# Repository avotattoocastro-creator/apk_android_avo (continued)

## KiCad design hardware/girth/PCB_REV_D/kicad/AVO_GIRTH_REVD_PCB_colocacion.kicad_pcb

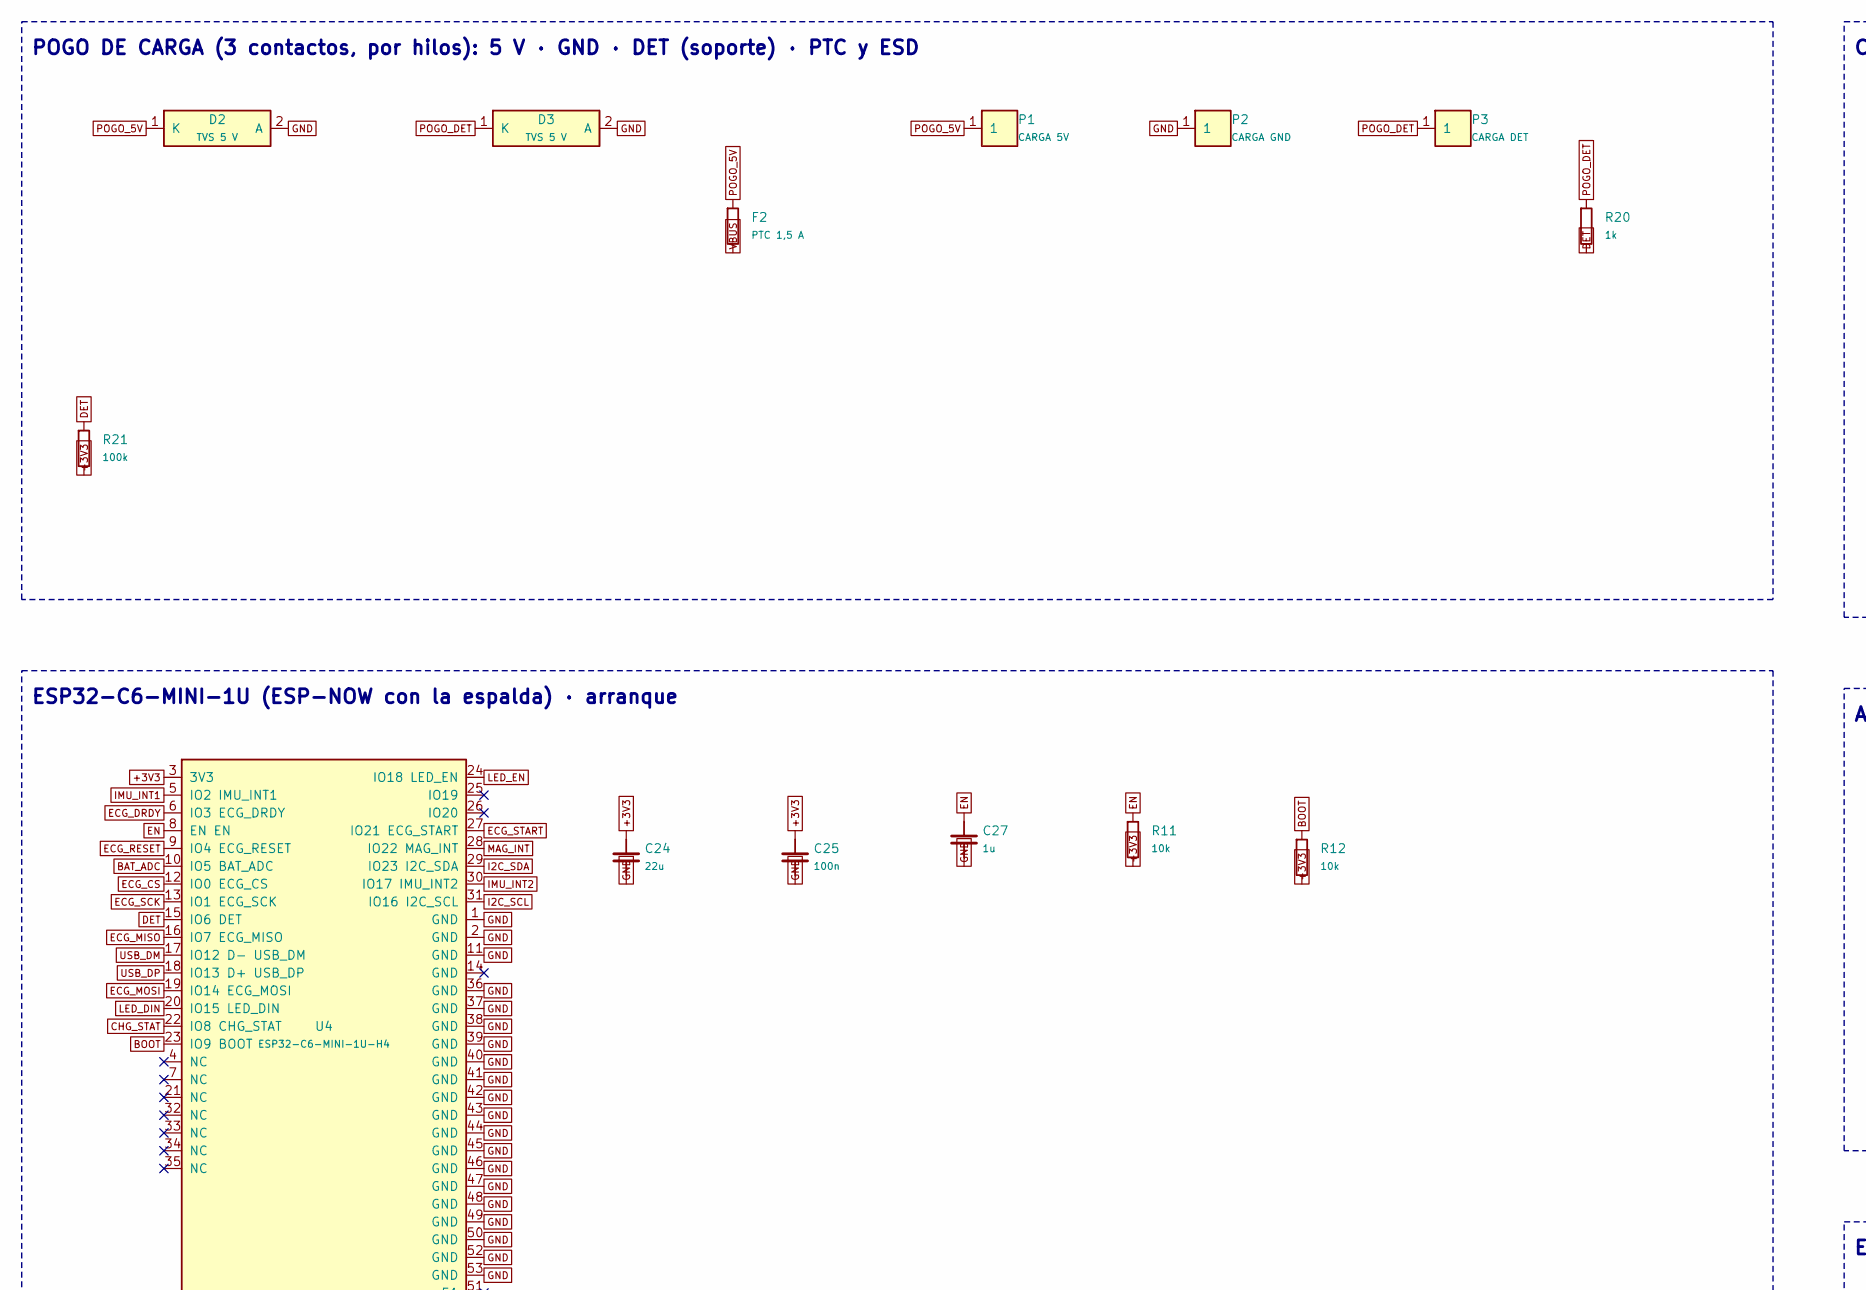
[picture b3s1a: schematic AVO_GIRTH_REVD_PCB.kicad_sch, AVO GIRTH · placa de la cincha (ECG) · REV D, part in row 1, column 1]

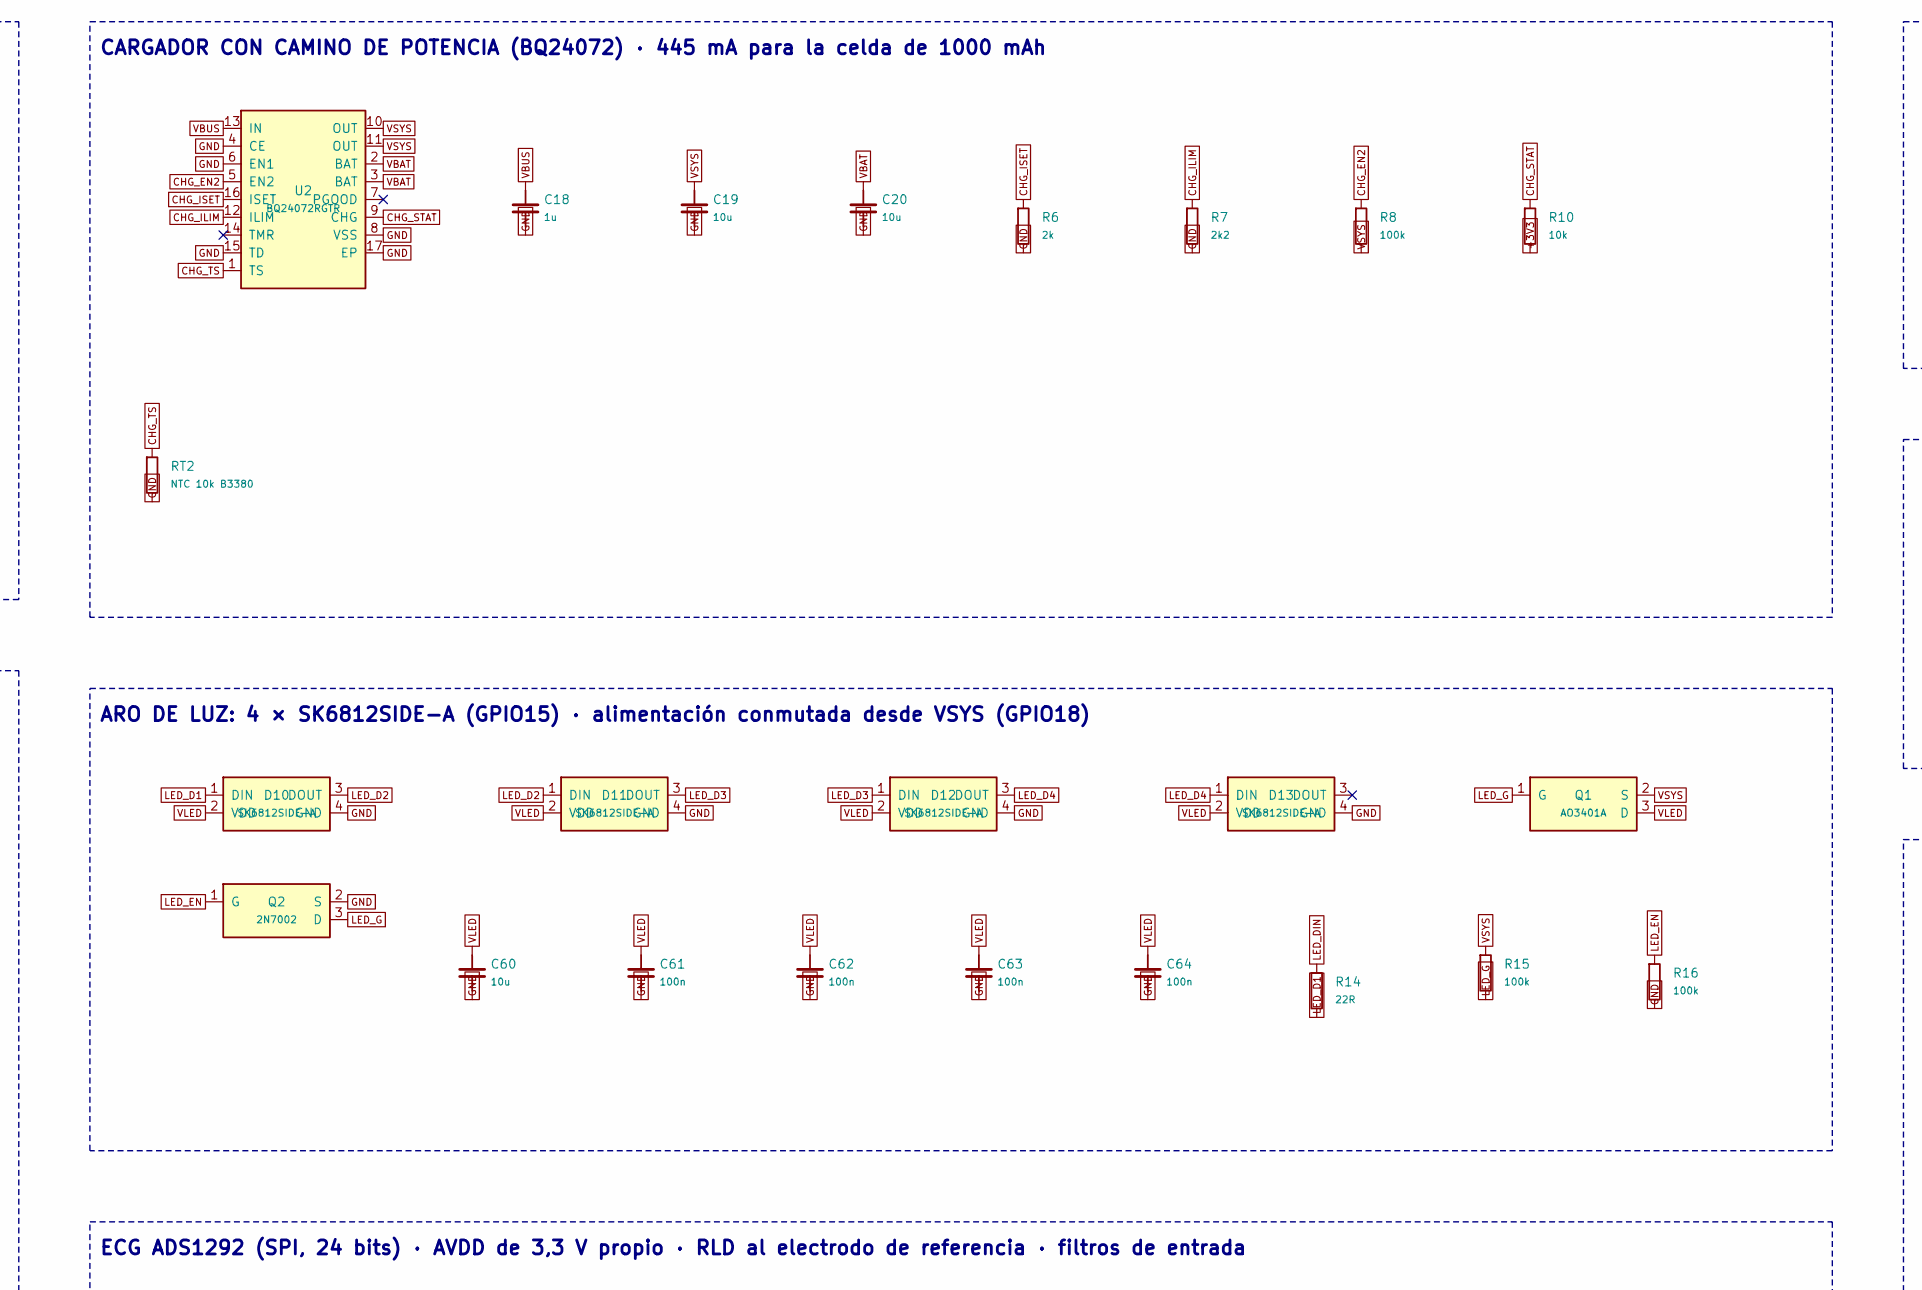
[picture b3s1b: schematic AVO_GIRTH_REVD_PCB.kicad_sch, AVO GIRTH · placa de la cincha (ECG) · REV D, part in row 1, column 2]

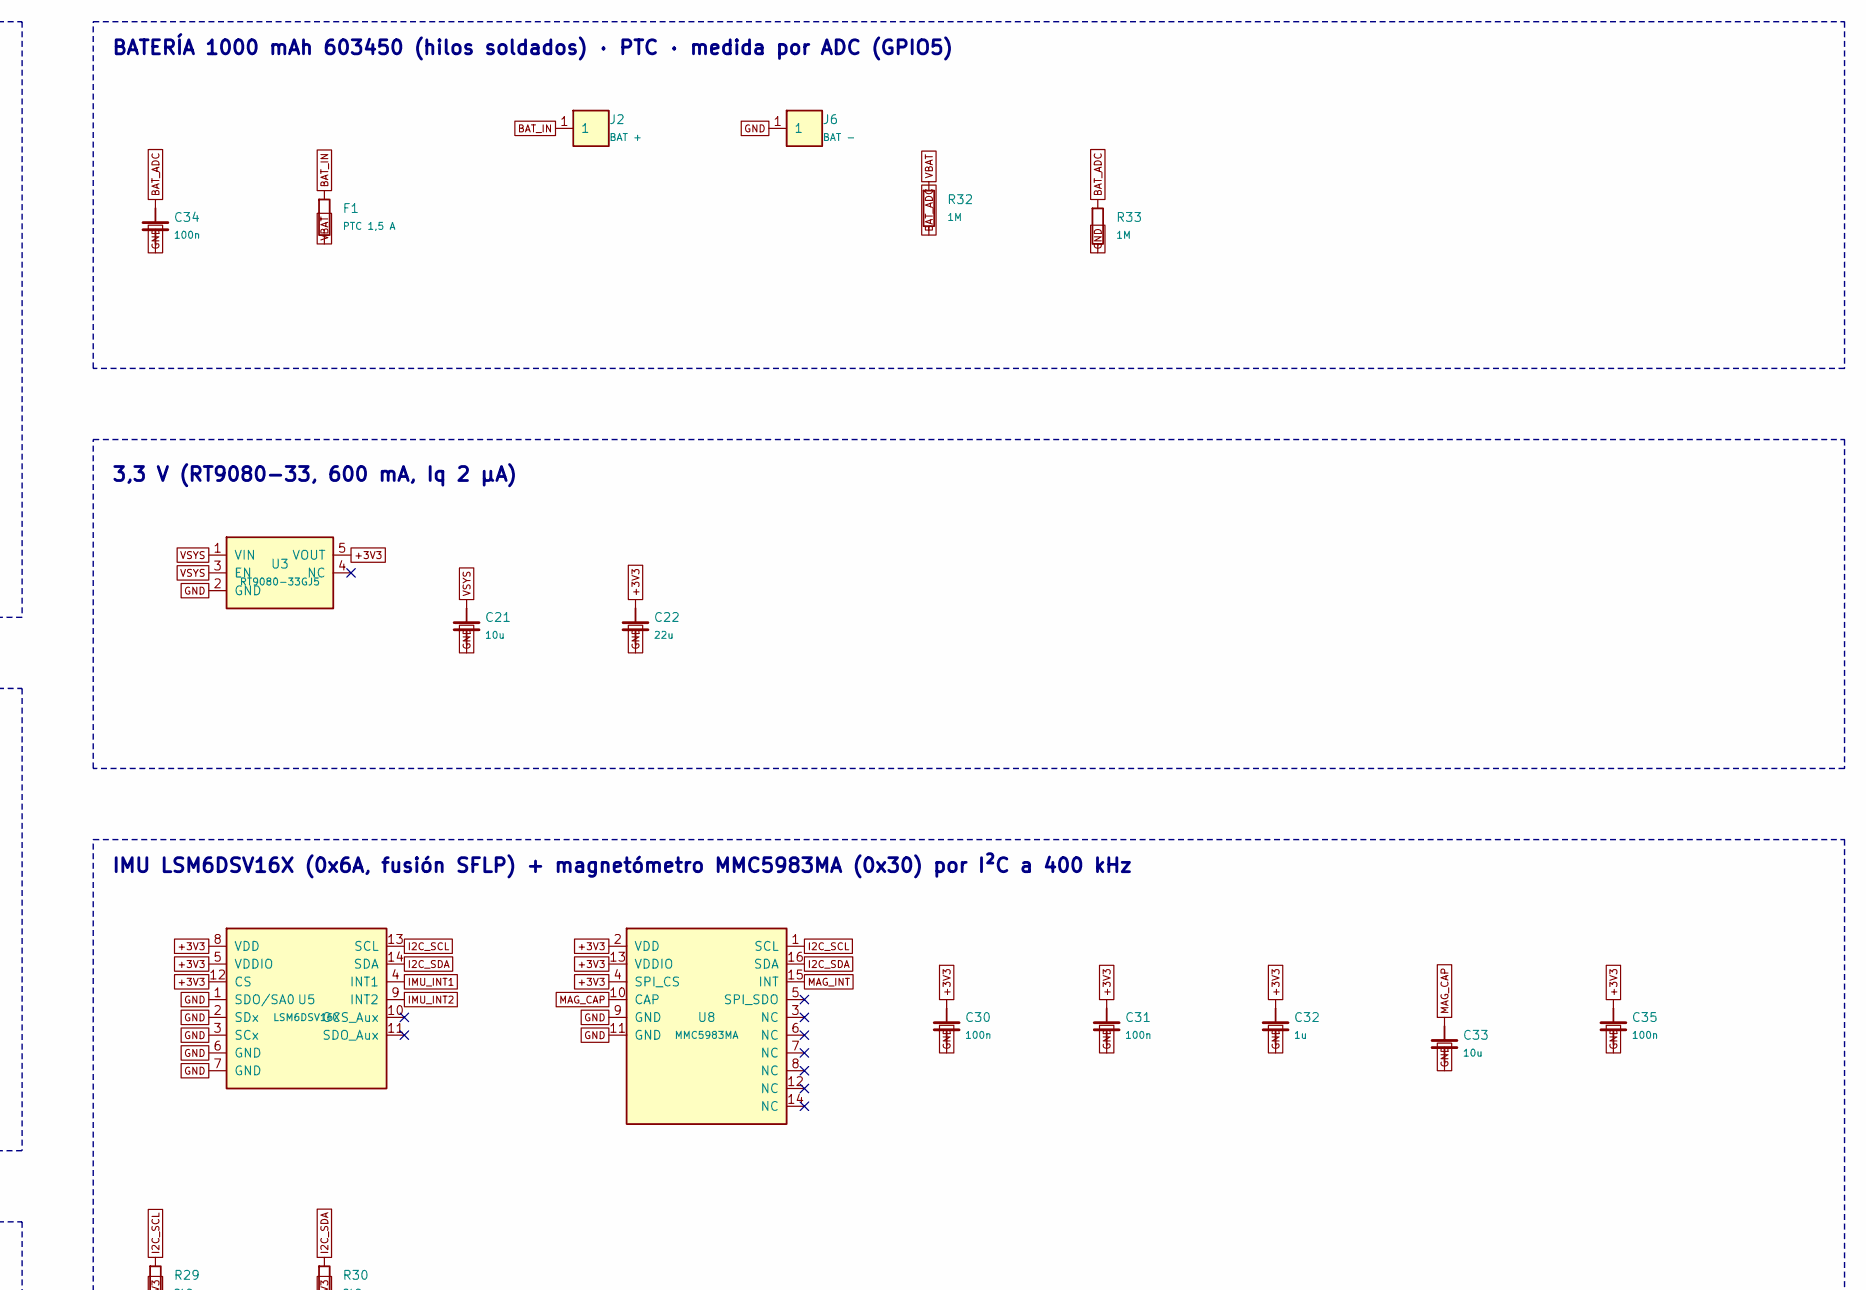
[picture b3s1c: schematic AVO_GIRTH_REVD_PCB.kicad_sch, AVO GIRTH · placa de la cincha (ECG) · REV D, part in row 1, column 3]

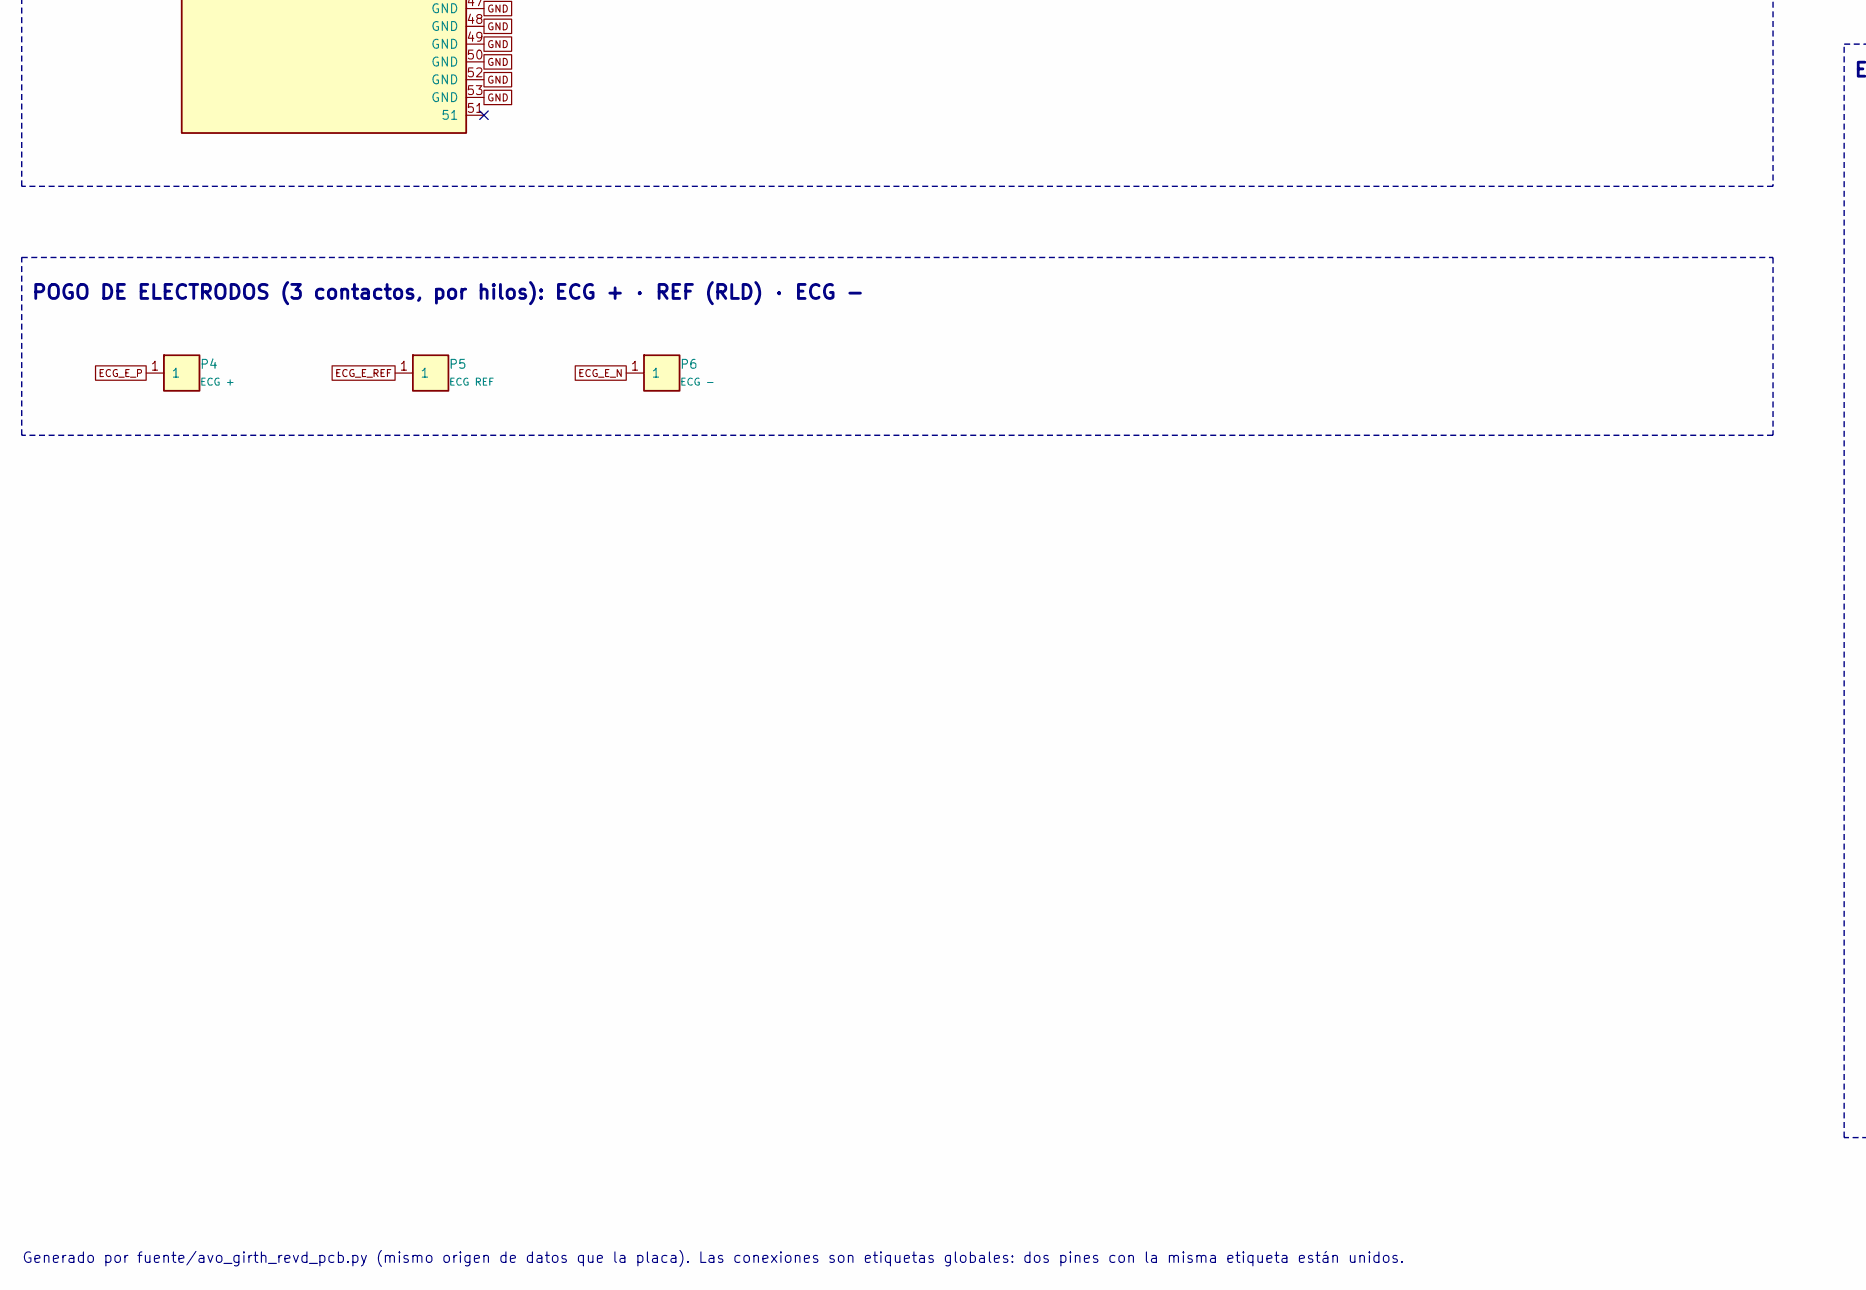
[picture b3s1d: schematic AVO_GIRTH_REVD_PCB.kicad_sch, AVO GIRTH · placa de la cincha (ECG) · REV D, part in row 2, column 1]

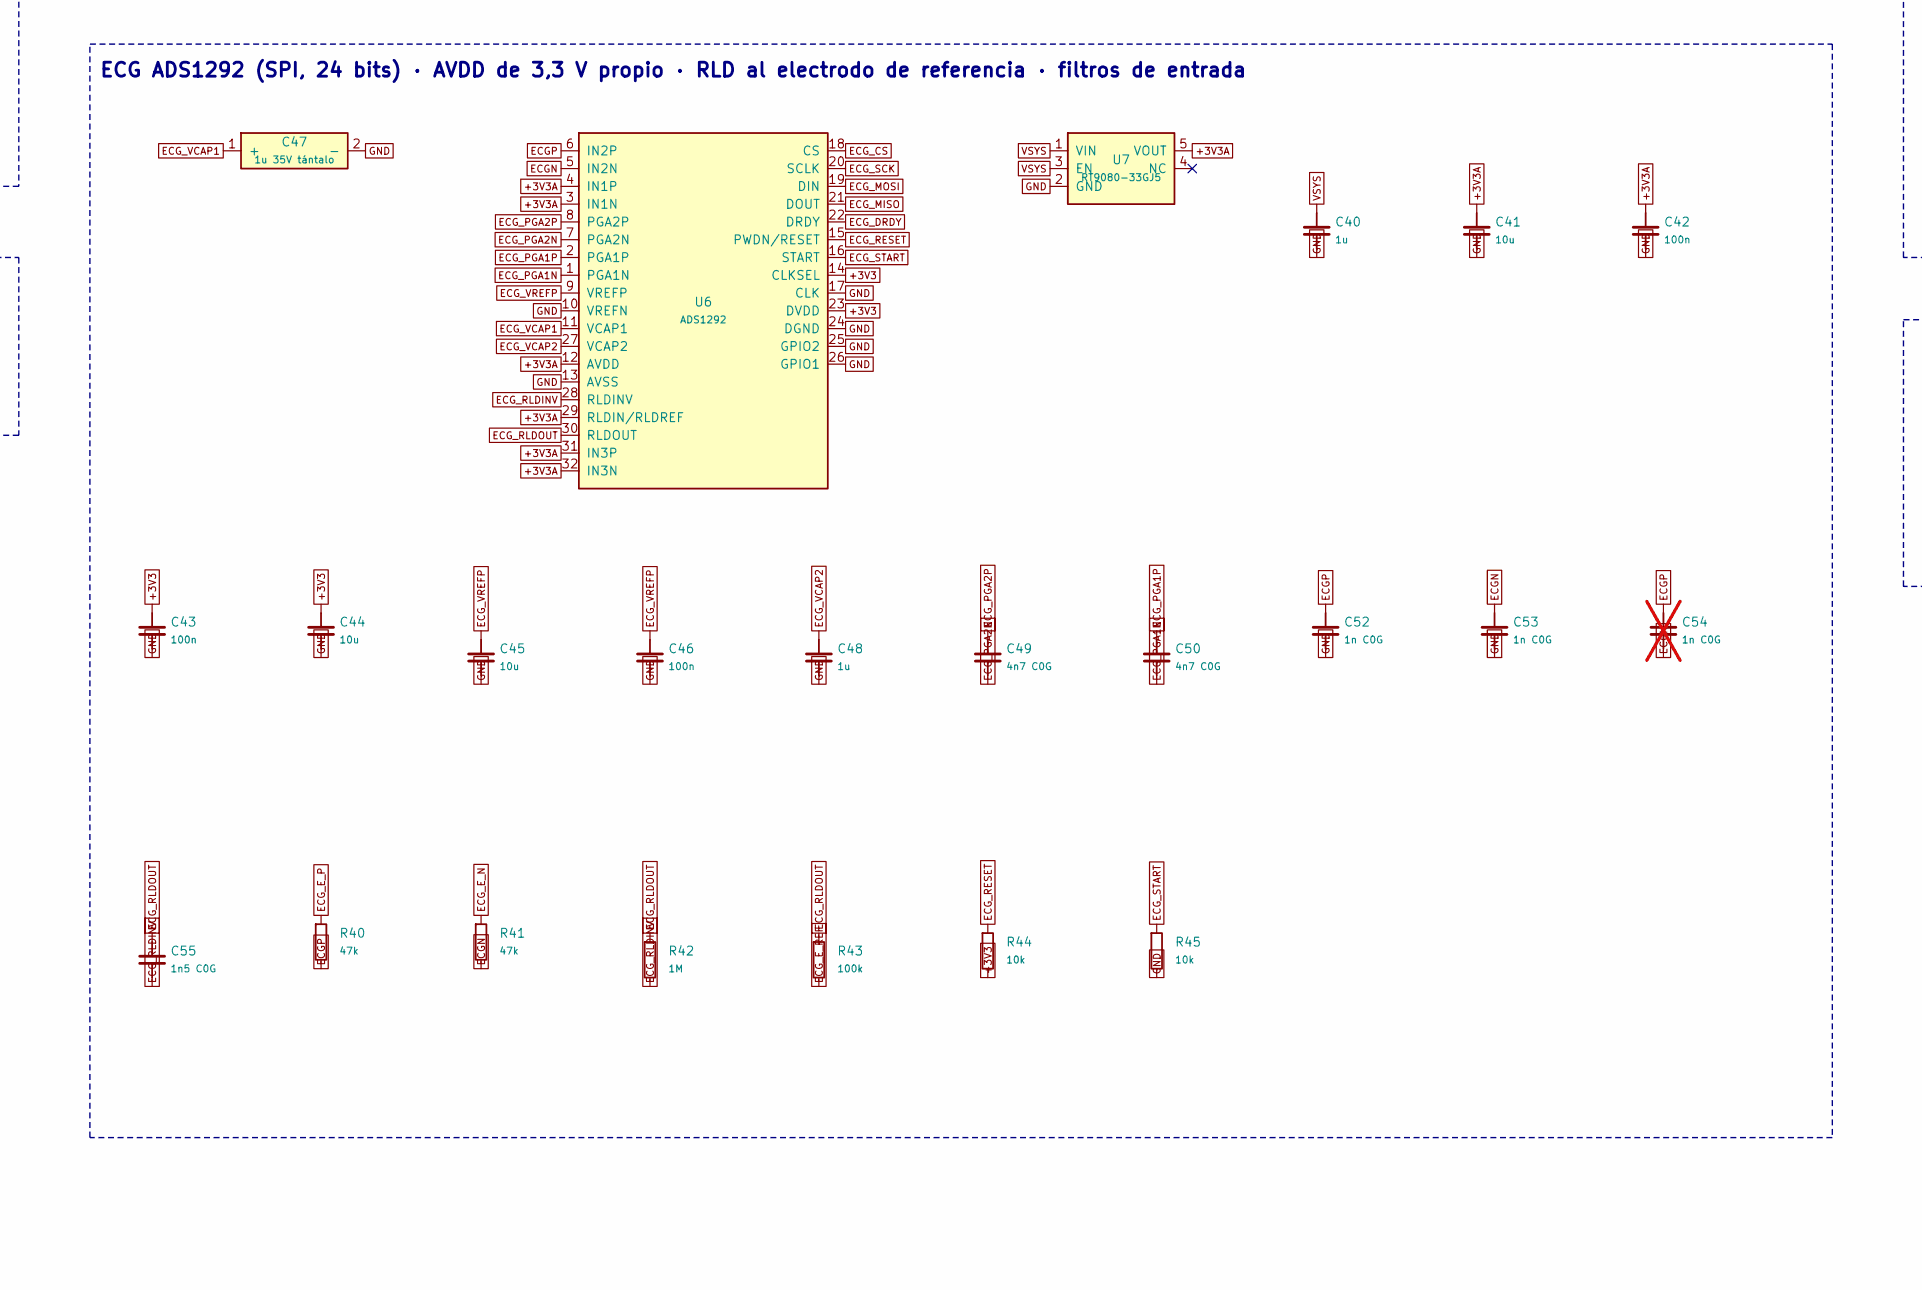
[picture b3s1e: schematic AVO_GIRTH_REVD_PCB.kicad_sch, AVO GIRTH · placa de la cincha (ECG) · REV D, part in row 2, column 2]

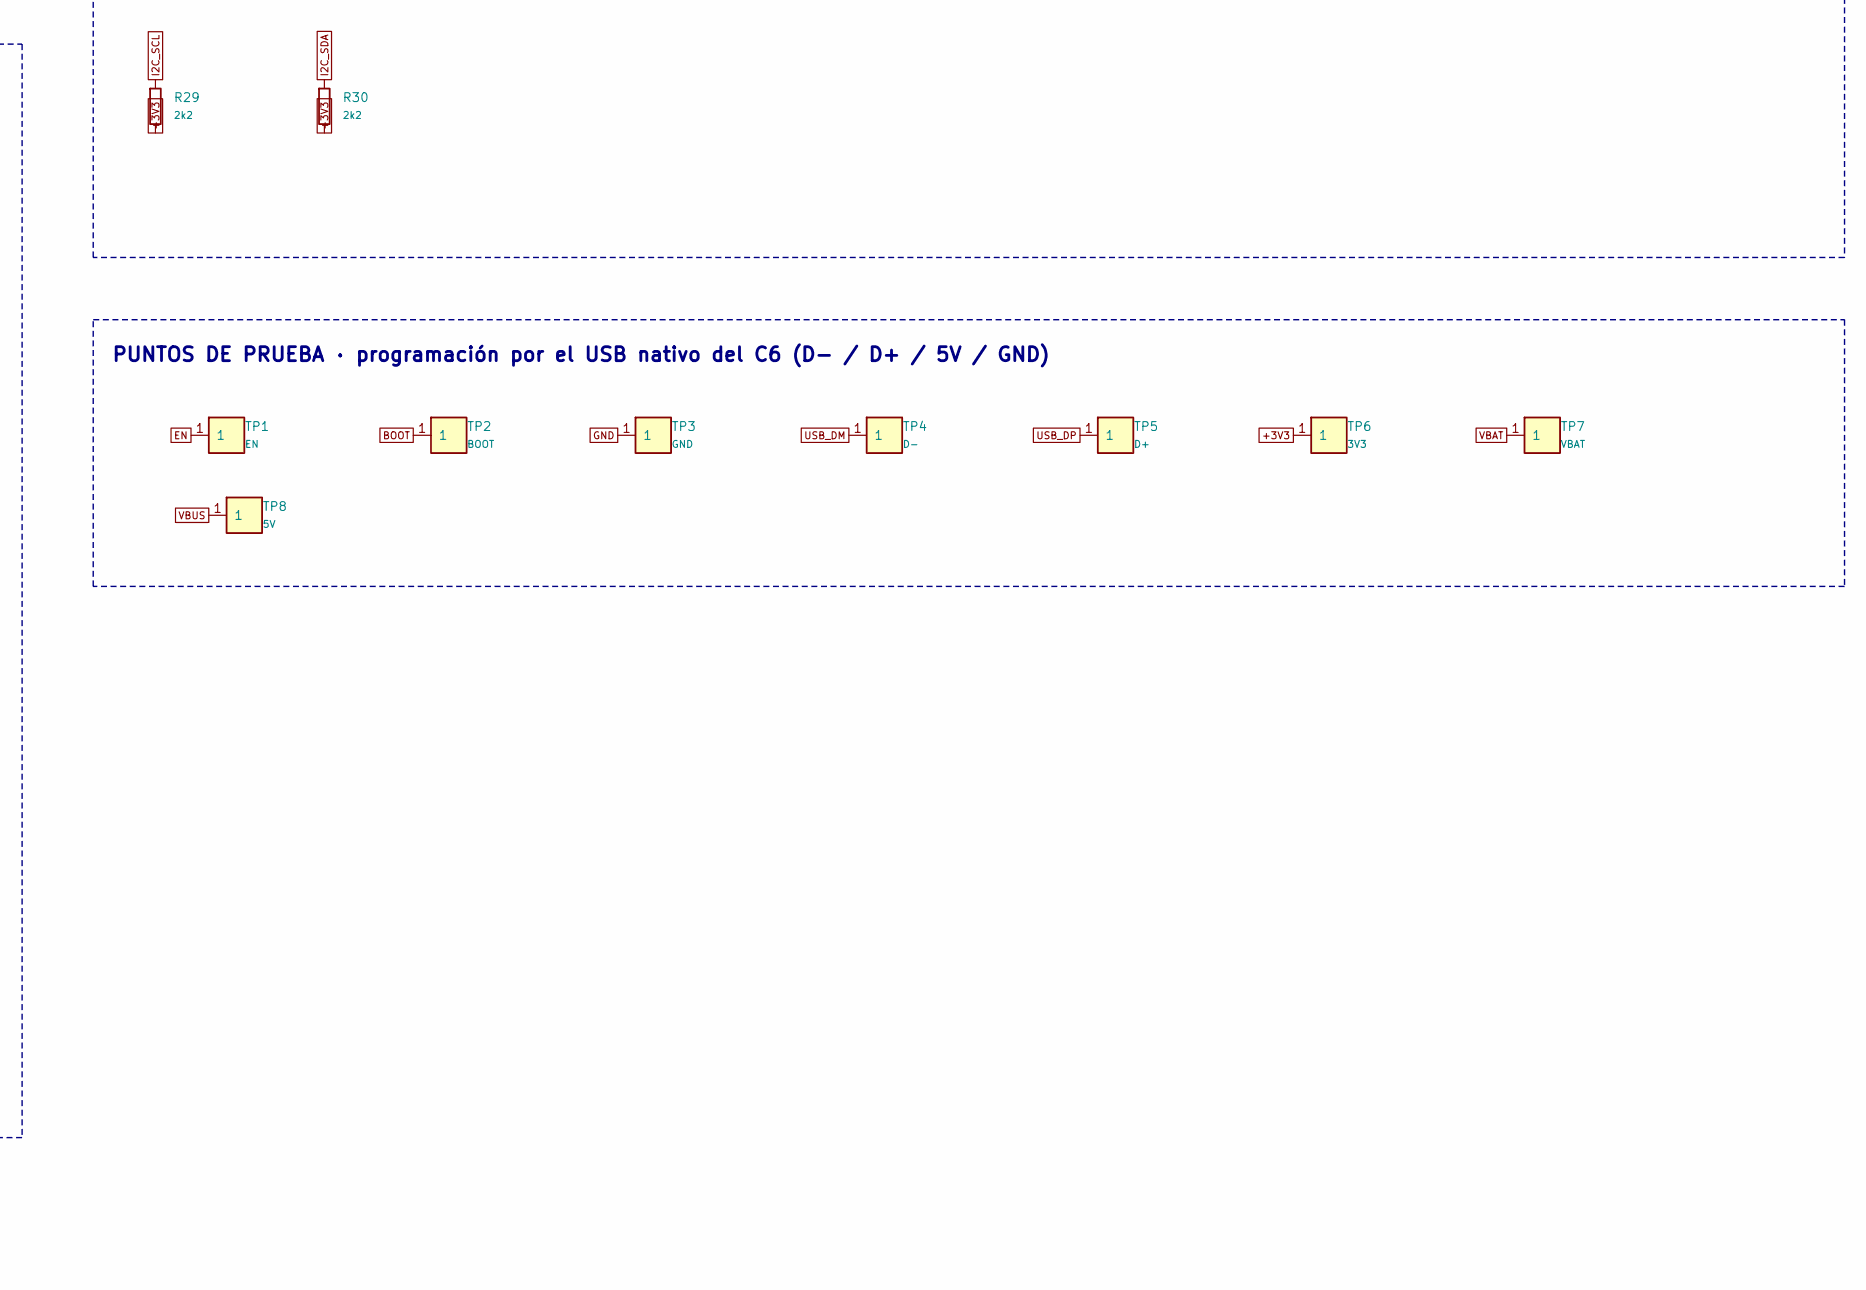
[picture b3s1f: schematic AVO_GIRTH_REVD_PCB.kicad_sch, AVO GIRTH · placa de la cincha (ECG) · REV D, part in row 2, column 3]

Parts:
C18, C27, C32, C40, C48: 1u; C_0402_1005Metric; LCSC C52923
C19, C20, C21, C33, C41, C44, C45, C60: 10u; C_0603_1608Metric; LCSC C96446
C22, C24: 22u; C_0805_2012Metric; LCSC C45783
C25, C30, C31, C34, C35, C42, C43, C46, C61, C62, C63, C64: 100n; C_0402_1005Metric; LCSC C1525
C47: 1u 35V tántalo; CP_EIA-3528-21_Kemet-B; MPN TAJB105K035RNJ (Kyocera AVX); LCSC C7192
C49, C50: 4n7 C0G; C_0603_1608Metric; LCSC C85980
C52, C53: 1n C0G; C_0402_1005Metric; LCSC C53547
C54: 1n C0G; C_0402_1005Metric; LCSC C53547; not fitted
C55: 1n5 C0G; C_0402_1005Metric; LCSC C668348
D2, D3: TVS 5 V; D_SOD-323; MPN PESD5V0S1BA; LCSC C2827694
D10, D11, D12, D13: SK6812SIDE-A; AVO_SK6812SIDE-A_4.0x1.6mm; MPN SK6812SIDE-A (OPSCO); LCSC C5378721
F1, F2: PTC 1,5 A; Fuse_1206_3216Metric; MPN SMD1206P150TF; LCSC C20802
J2: BAT +; WirePad_D1.5_Drill0.8
J6: BAT -; WirePad_D1.5_Drill0.8
P1: CARGA 5V; WirePad_D1.5_Drill0.8
P2: CARGA GND; WirePad_D1.5_Drill0.8
P3: CARGA DET; WirePad_D1.5_Drill0.8
P4: ECG +; WirePad_D1.5_Drill0.8
P5: ECG REF; WirePad_D1.5_Drill0.8
P6: ECG -; WirePad_D1.5_Drill0.8
Q1: AO3401A; SOT-23; MPN AO3401A (P, 30 V, 4 A); LCSC C15127
Q2: 2N7002; SOT-23; MPN 2N7002 (N); LCSC C8545
R6: 2k; R_0402_1005Metric; LCSC C4109
R7, R29, R30: 2k2; R_0402_1005Metric; LCSC C25879
R8, R15, R16, R21, R43: 100k; R_0402_1005Metric; LCSC C25741
R10, R11, R12, R44, R45: 10k; R_0402_1005Metric; LCSC C25744
R14: 22R; R_0402_1005Metric; LCSC C25092
R20: 1k; R_0402_1005Metric; LCSC C11702
R32, R33, R42: 1M; R_0402_1005Metric; LCSC C26083
R40, R41: 47k; R_0402_1005Metric; LCSC C25792
RT2: NTC 10k B3380; R_0402_1005Metric; MPN NCP15XH103F03RC; LCSC C77131
TP1: EN; TestPoint_Pad_D1.0mm
TP2: BOOT; TestPoint_Pad_D1.0mm
TP3: GND; TestPoint_Pad_D1.0mm
TP4: D-; TestPoint_Pad_D1.0mm
TP5: D+; TestPoint_Pad_D1.0mm
TP6: 3V3; TestPoint_Pad_D1.0mm
TP7: VBAT; TestPoint_Pad_D1.0mm
TP8: 5V; TestPoint_Pad_D1.0mm
U2: BQ24072RGTR; VQFN-16-1EP_3x3mm_P0.5mm_EP1.68x1.68mm_ThermalVias; MPN BQ24072RGTR; LCSC C140288
U3, U7: RT9080-33GJ5; SOT-23-5; MPN RT9080-33GJ5; LCSC C841192
U4: ESP32-C6-MINI-1U-H4; ESP32-C6-MINI-1U; MPN ESP32-C6-MINI-1U-H4 (alt. -N4); LCSC C20627095
U5: LSM6DSV16X; ST_LGA-14L_2.5x3mm_P0.5mm; MPN LSM6DSV16XTR (ST); LCSC C5267406
U6: ADS1292; AVO_TQFP-32_5x5mm_P0.5mm; MPN ADS1292IPBSR (TI, TQFP-32) · alt. ADS12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; LCSC C2651570
U8: MMC5983MA; MEMSIC_MMC5983MA_LGA-16_3x3mm_P0.5mm; MPN MMC5983MA (MEMSIC); LCSC C404329

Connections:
+3V3: C22.1, C24.1, C25.1, C30.1, C31.1, C32.1, C35.1, C43.1, C44.1, R10.2, R11.2, R12.2, R21.2, R29.2, R30.2, R44.2, TP6.1, U3.5 (VOUT), U4.3 (3V3), U5.5 (VDDIO), U5.8 (VDD), U5.12 (CS), U6.14 (CLKSEL), U6.23 (DVDD), U8.2 (VDD), U8.4 (SPI_CS), U8.13 (VDDIO)
+3V3A: C41.1, C42.1, U6.3 (IN1N), U6.4 (IN1P), U6.12 (AVDD), U6.29 (RLDIN/RLDREF), U6.31 (IN3P), U6.32 (IN3N), U7.5 (VOUT)
BAT_ADC: C34.1, R32.2, R33.1, U4.10 (IO5 BAT_ADC)
BAT_IN: F1.1, J2.1
BOOT: R12.1, TP2.1, U4.23 (IO9 BOOT)
CHG_EN2: R8.1, U2.5 (EN2)
CHG_ILIM: R7.1, U2.12 (ILIM)
CHG_ISET: R6.1, U2.16 (ISET)
CHG_STAT: R10.1, U2.9 (CHG), U4.22 (IO8 CHG_STAT)
CHG_TS: RT2.1, U2.1 (TS)
DET: R20.2, R21.1, U4.15 (IO6 DET)
ECGN: C53.1, C54.2, R41.2, U6.5 (IN2N)
ECGP: C52.1, C54.1, R40.2, U6.6 (IN2P)
ECG_CS: U4.12 (IO0 ECG_CS), U6.18 (CS)
ECG_DRDY: U4.6 (IO3 ECG_DRDY), U6.22 (DRDY)
ECG_E_N: P6.1, R41.1
ECG_E_P: P4.1, R40.1
ECG_E_REF: P5.1, R43.2
ECG_MISO: U4.16 (IO7 ECG_MISO), U6.21 (DOUT)
ECG_MOSI: U4.19 (IO14 ECG_MOSI), U6.19 (DIN)
ECG_PGA1N: C50.2, U6.1 (PGA1N)
ECG_PGA1P: C50.1, U6.2 (PGA1P)
ECG_PGA2N: C49.2, U6.7 (PGA2N)
ECG_PGA2P: C49.1, U6.8 (PGA2P)
ECG_RESET: R44.1, U4.9 (IO4 ECG_RESET), U6.15 (PWDN/RESET)
ECG_RLDINV: C55.2, R42.2, U6.28 (RLDINV)
ECG_RLDOUT: C55.1, R42.1, R43.1, U6.30 (RLDOUT)
ECG_SCK: U4.13 (IO1 ECG_SCK), U6.20 (SCLK)
ECG_START: R45.1, U4.27 (IO21 ECG_START), U6.16 (START)
ECG_VCAP1: C47.1 (+), U6.11 (VCAP1)
ECG_VCAP2: C48.1, U6.27 (VCAP2)
ECG_VREFP: C45.1, C46.1, U6.9 (VREFP)
EN: C27.1, R11.1, TP1.1, U4.8 (EN EN)
GND: C18.2, C19.2, C20.2, C21.2, C22.2, C24.2, C25.2, C27.2, C30.2, C31.2, C32.2, C33.2, C34.2, C35.2, C40.2, C41.2, C42.2, C43.2, C44.2, C45.2, C46.2, C47.2 (−), C48.2, C52.2, C53.2, C60.2, C61.2, C62.2, C63.2, C64.2, D2.2 (A), D3.2 (A), D10.4 (GND), D11.4 (GND), D12.4 (GND), D13.4 (GND), J6.1, P2.1, Q2.2 (S), R6.2, R7.2, R16.2, R33.2, R45.2, RT2.2, TP3.1, U2.4 (CE), U2.6 (EN1), U2.8 (VSS), U2.15 (TD), U2.17 (EP), U3.2 (GND), U4.1 (GND), U4.2 (GND), U4.11 (GND), U4.36 (GND), U4.37 (GND), U4.38 (GND), U4.39 (GND), U4.40 (GND), U4.41 (GND), U4.42 (GND), U4.43 (GND), U4.44 (GND), U4.45 (GND), U4.46 (GND), U4.47 (GND), U4.48 (GND), U4.49 (GND), U4.50 (GND), U4.52 (GND), U4.53 (GND), U5.1 (SDO/SA0), U5.2 (SDx), U5.3 (SCx), U5.6 (GND), U5.7 (GND), U6.10 (VREFN), U6.13 (AVSS), U6.17 (CLK), U6.24 (DGND), U6.25 (GPIO2), U6.26 (GPIO1), U7.2 (GND), U8.9 (GND), U8.11 (GND)
I2C_SCL: R29.1, U4.31 (IO16 I2C_SCL), U5.13 (SCL), U8.1 (SCL)
I2C_SDA: R30.1, U4.29 (IO23 I2C_SDA), U5.14 (SDA), U8.16 (SDA)
IMU_INT1: U4.5 (IO2 IMU_INT1), U5.4 (INT1)
IMU_INT2: U4.30 (IO17 IMU_INT2), U5.9 (INT2)
LED_D1: D10.1 (DIN), R14.2
LED_D2: D10.3 (DOUT), D11.1 (DIN)
LED_D3: D11.3 (DOUT), D12.1 (DIN)
LED_D4: D12.3 (DOUT), D13.1 (DIN)
LED_DIN: R14.1, U4.20 (IO15 LED_DIN)
LED_EN: Q2.1 (G), R16.1, U4.24 (IO18 LED_EN)
LED_G: Q1.1 (G), Q2.3 (D), R15.2
MAG_CAP: C33.1, U8.10 (CAP)
MAG_INT: U4.28 (IO22 MAG_INT), U8.15 (INT)
POGO_5V: D2.1 (K), F2.1, P1.1
POGO_DET: D3.1 (K), P3.1, R20.1
USB_DM: TP4.1, U4.17 (IO12 D- USB_DM)
USB_DP: TP5.1, U4.18 (IO13 D+ USB_DP)
VBAT: C20.1, F1.2, R32.1, TP7.1, U2.2 (BAT), U2.3 (BAT)
VBUS: C18.1, F2.2, TP8.1, U2.13 (IN)
VLED: C60.1, C61.1, C62.1, C63.1, C64.1, D10.2 (VDD), D11.2 (VDD), D12.2 (VDD), D13.2 (VDD), Q1.3 (D)
VSYS: C19.1, C21.1, C40.1, Q1.2 (S), R8.2, R15.1, U2.10 (OUT), U2.11 (OUT), U3.1 (VIN), U3.3 (EN), U7.1 (VIN), U7.3 (EN)

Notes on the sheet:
ECG ADS1292 (SPI, 24 bits) · AVDD de 3,3 V propio · RLD al electrodo de referencia · filtros de entrada
POGO DE CARGA (3 contactos, por hilos): 5 V · GND · DET (soporte) · PTC y ESD
ARO DE LUZ: 4 × SK6812SIDE-A (GPIO15) · alimentación conmutada desde VSYS (GPIO18)
CARGADOR CON CAMINO DE POTENCIA (BQ24072) · 445 mA para la celda de 1000 mAh
3,3 V (RT9080-33, 600 mA, Iq 2 µA)
ESP32-C6-MINI-1U (ESP-NOW con la espalda) · arranque
IMU LSM6DSV16X (0x6A, fusión SFLP) + magnetómetro MMC5983MA (0x30) por I²C a 400 kHz
BATERÍA 1000 mAh 603450 (hilos soldados) · PTC · medida por ADC (GPIO5)
POGO DE ELECTRODOS (3 contactos, por hilos): ECG + · REF (RLD) · ECG −
PUNTOS DE PRUEBA · programación por el USB nativo del C6 (D− / D+ / 5V / GND)
Generado por fuente/avo_girth_revd_pcb.py (mismo origen de datos que la placa). Las conexiones son etiquetas globales: dos pines con la misma etiqueta están unidos.

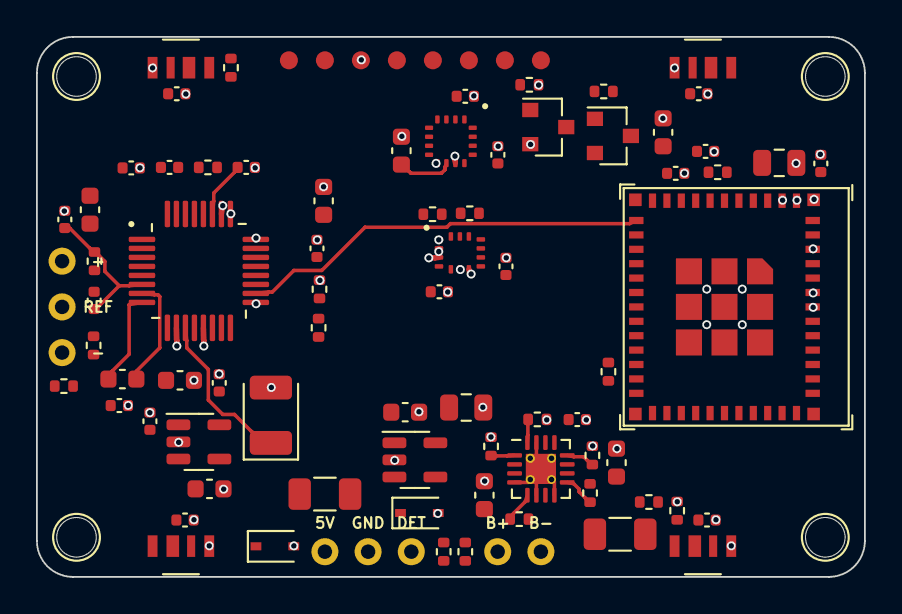
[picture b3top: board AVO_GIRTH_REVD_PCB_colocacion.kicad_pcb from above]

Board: 4 copper layers, 46.0 x 30.0 mm, 93 parts (0 on the bottom side), 55 nets.

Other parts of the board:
H1, H2, H3, H4: TALADRO M2; AVO_Taladro_NPTH_D2.2
